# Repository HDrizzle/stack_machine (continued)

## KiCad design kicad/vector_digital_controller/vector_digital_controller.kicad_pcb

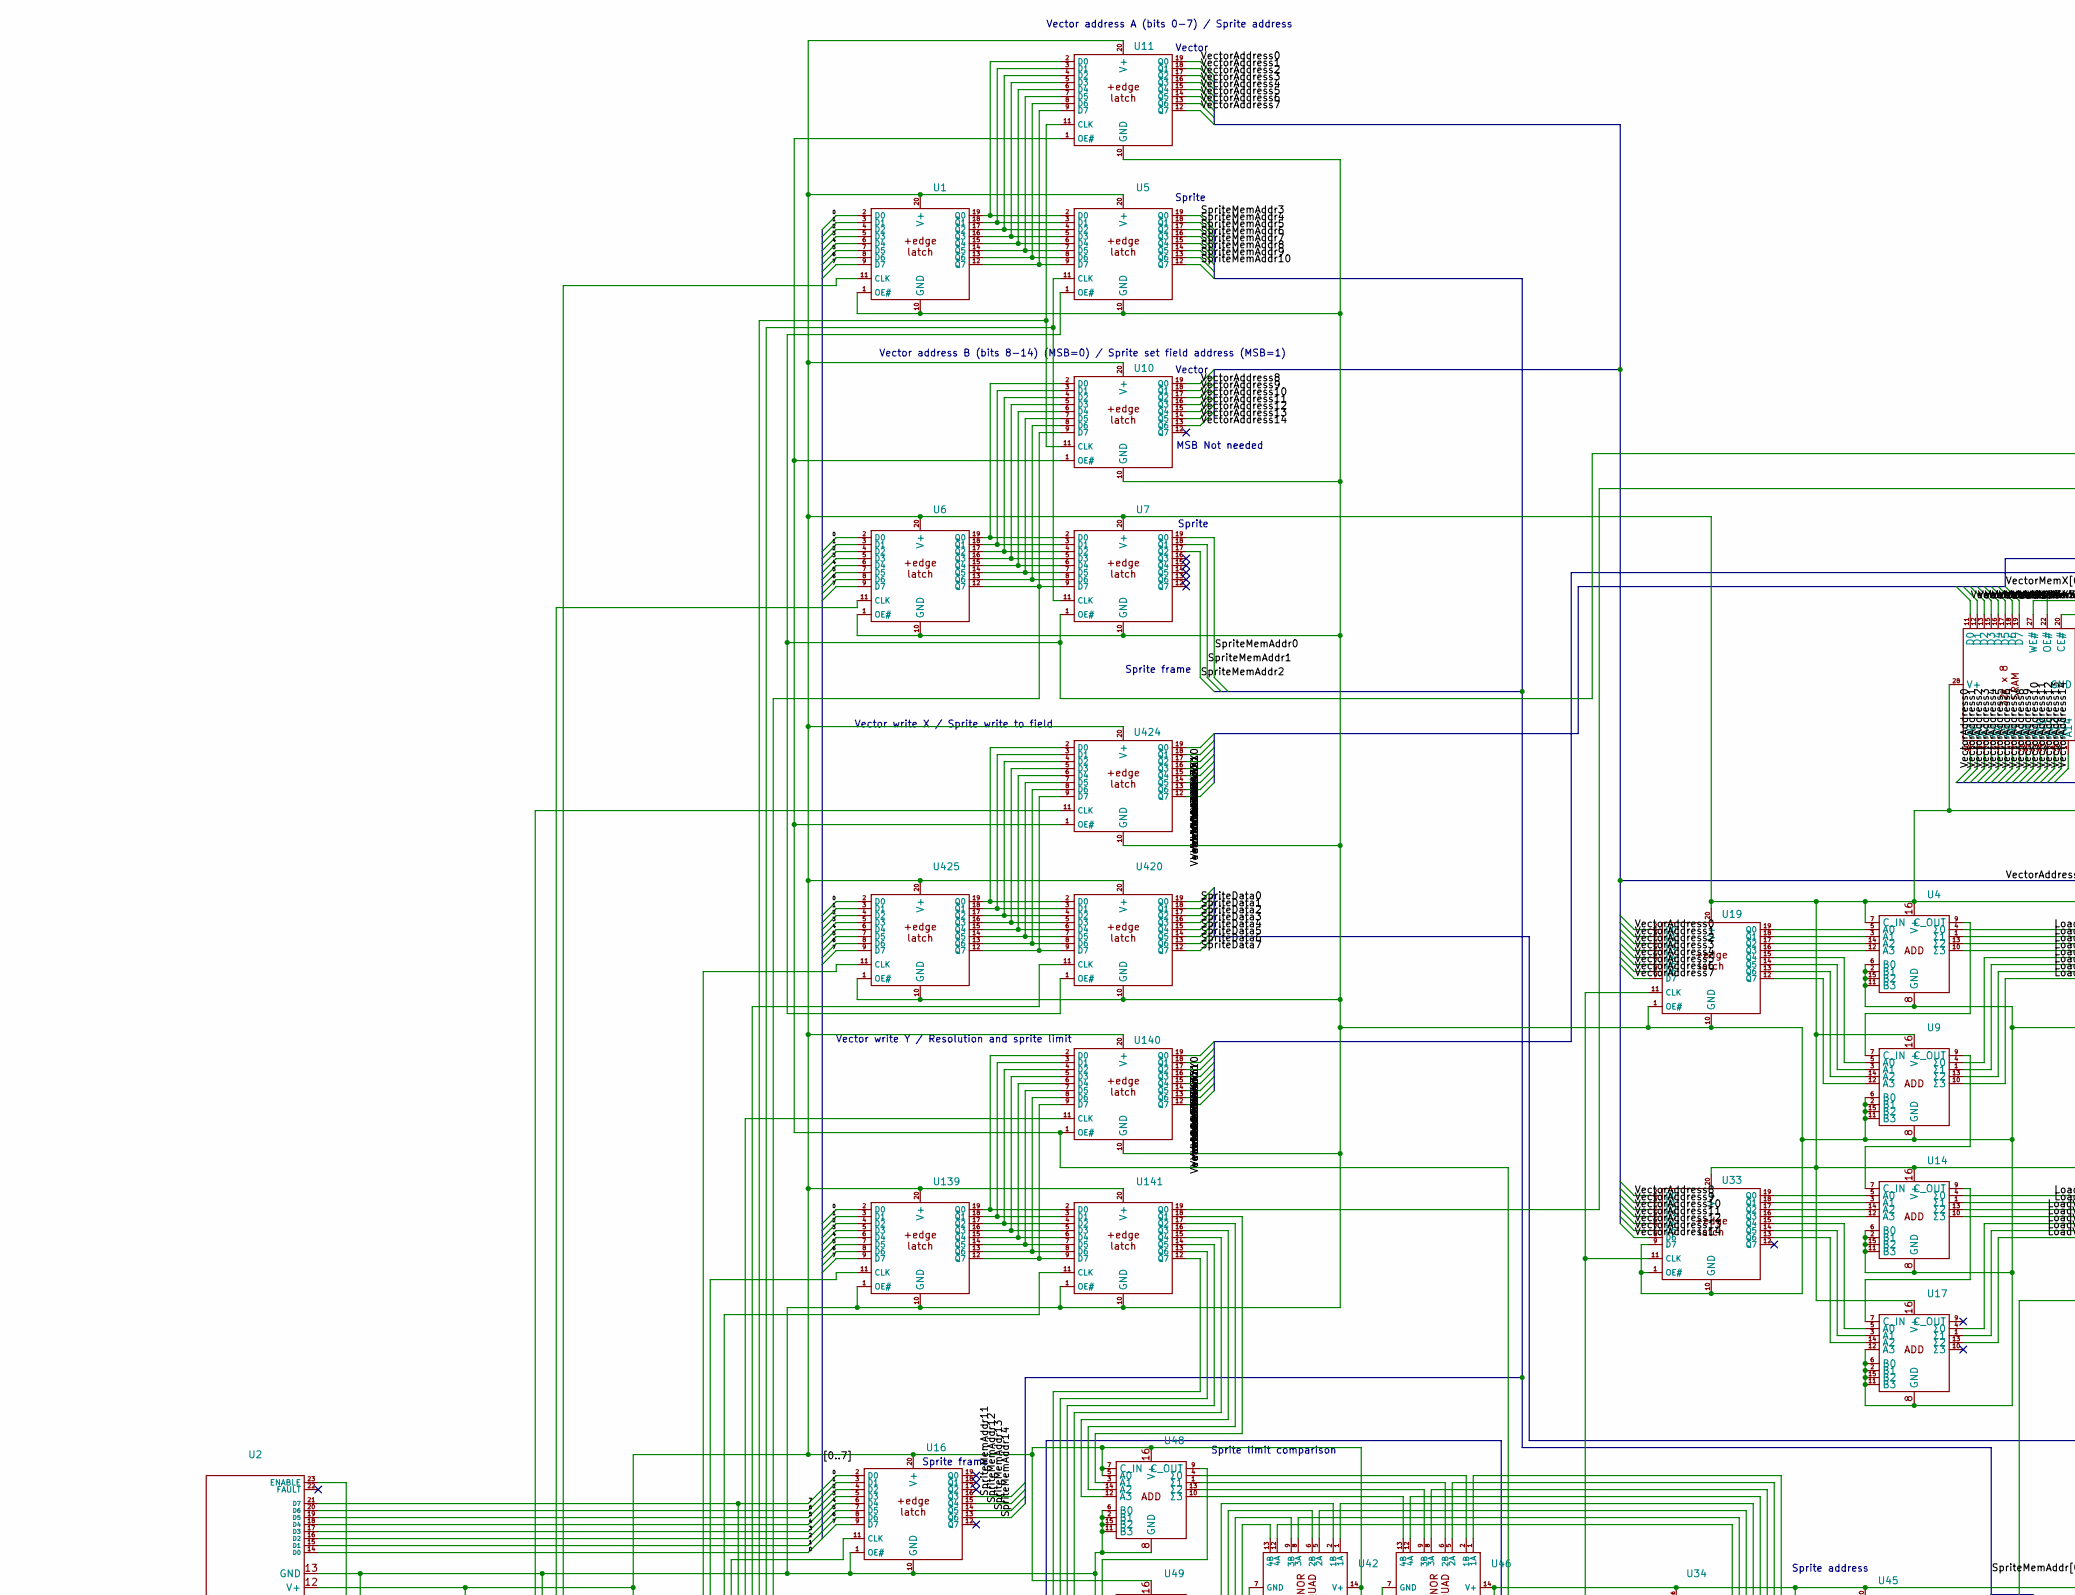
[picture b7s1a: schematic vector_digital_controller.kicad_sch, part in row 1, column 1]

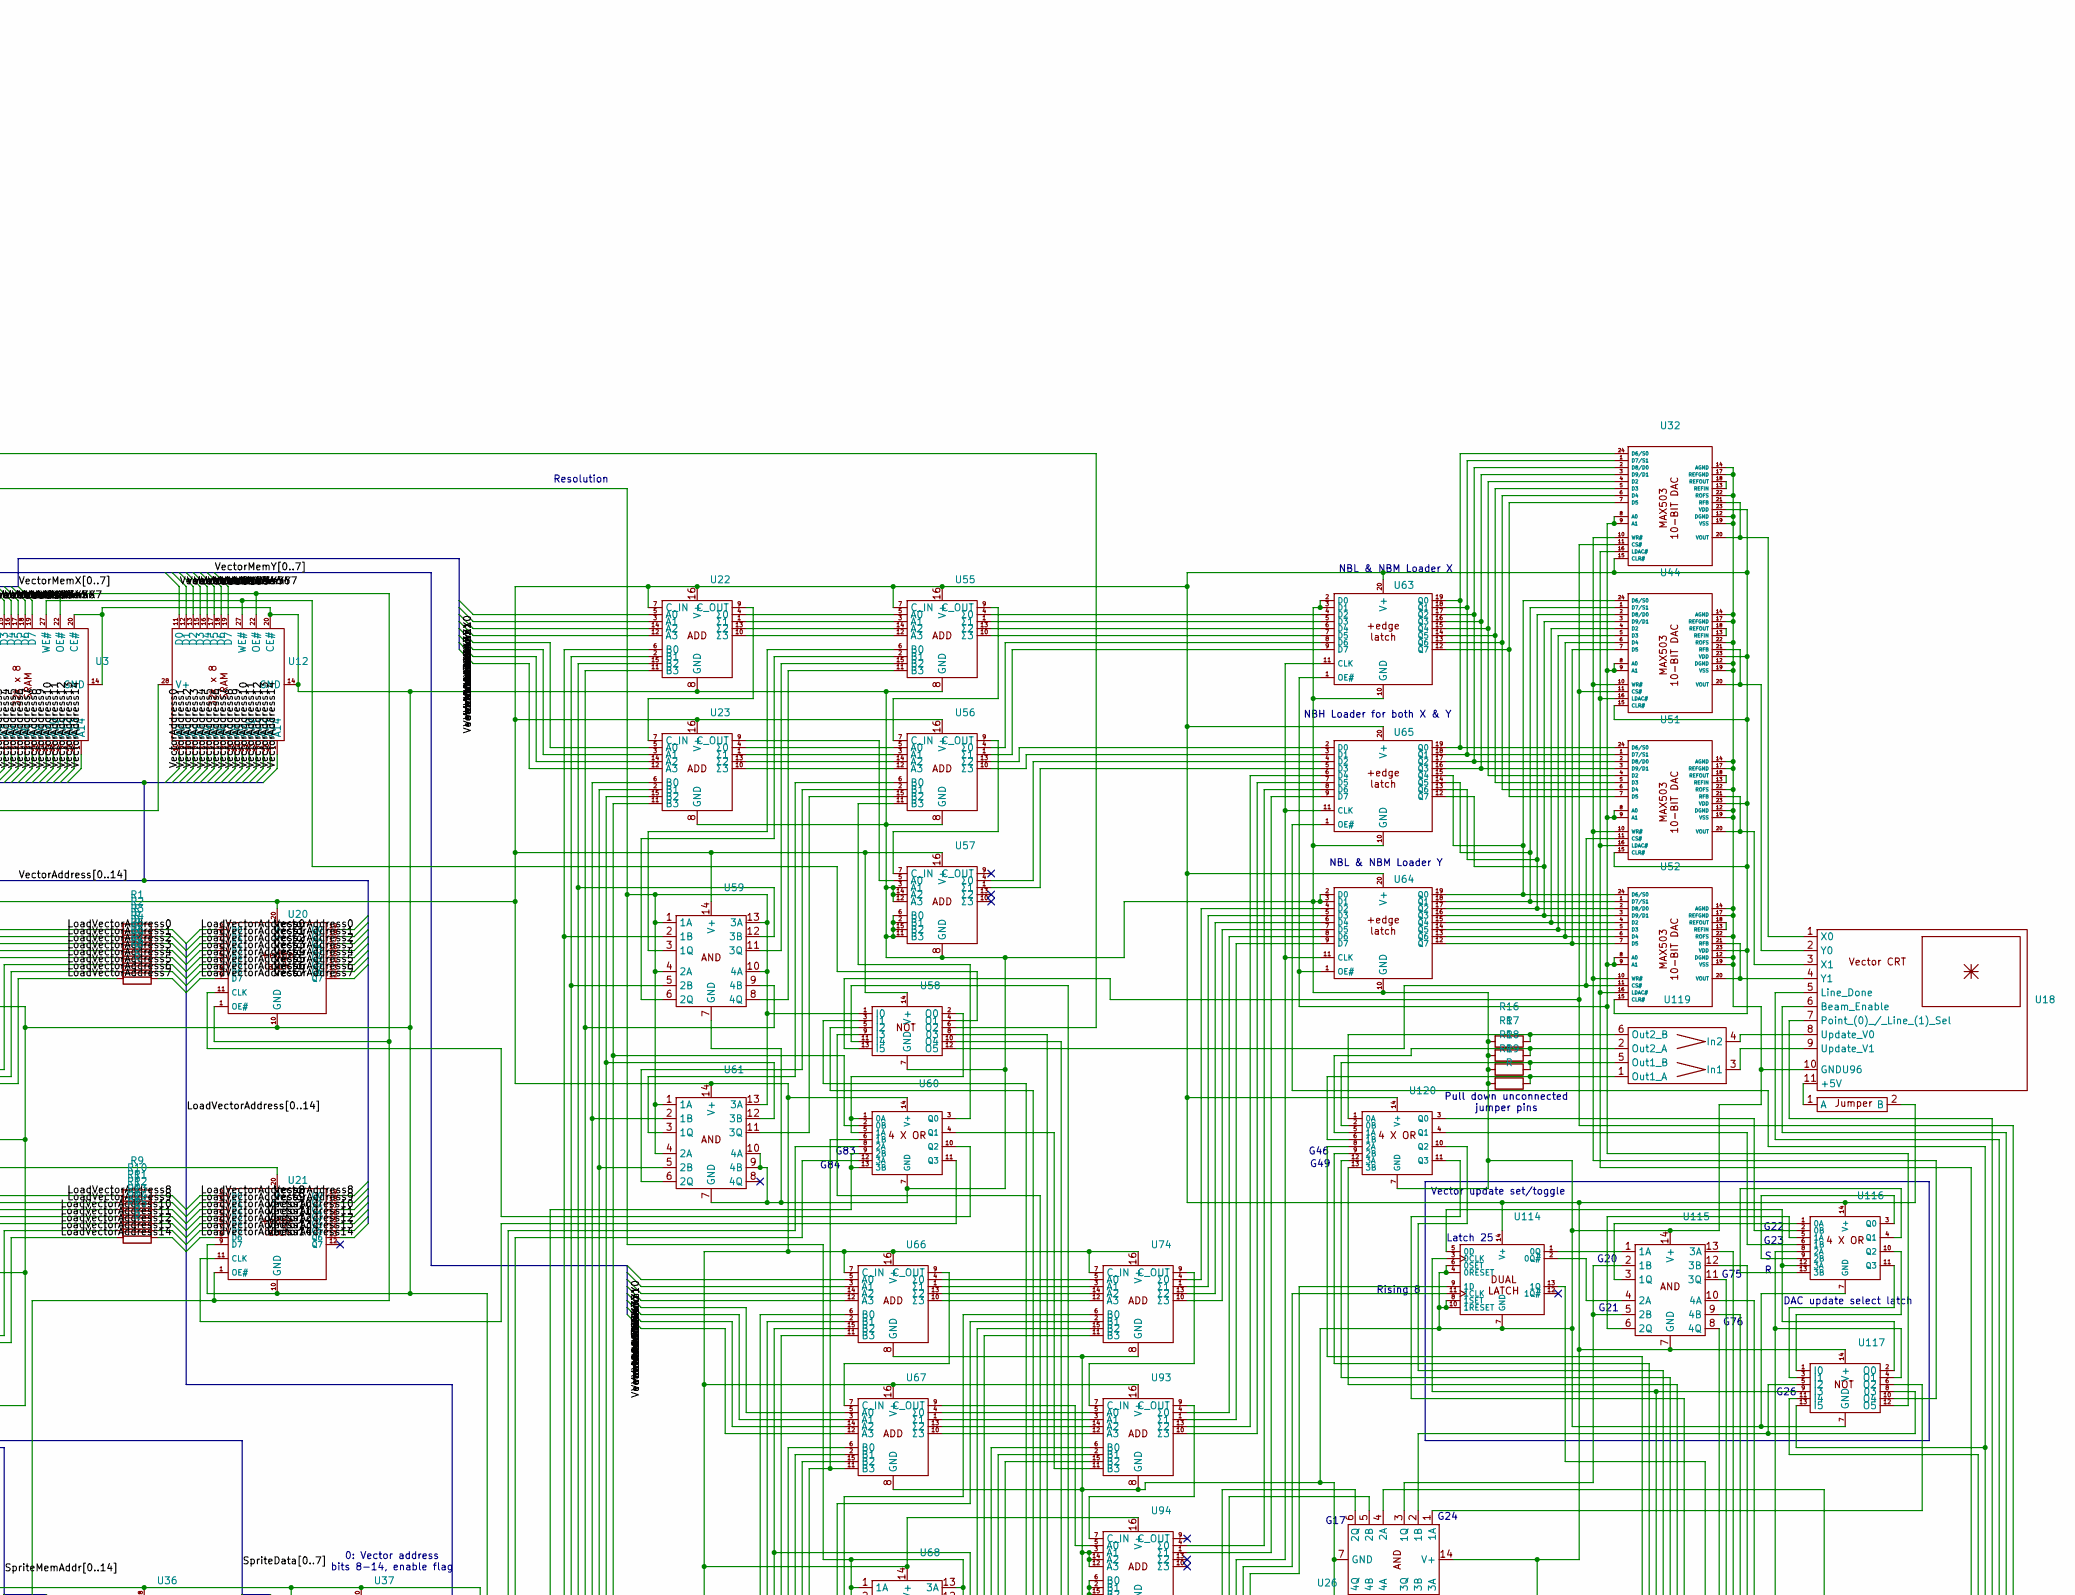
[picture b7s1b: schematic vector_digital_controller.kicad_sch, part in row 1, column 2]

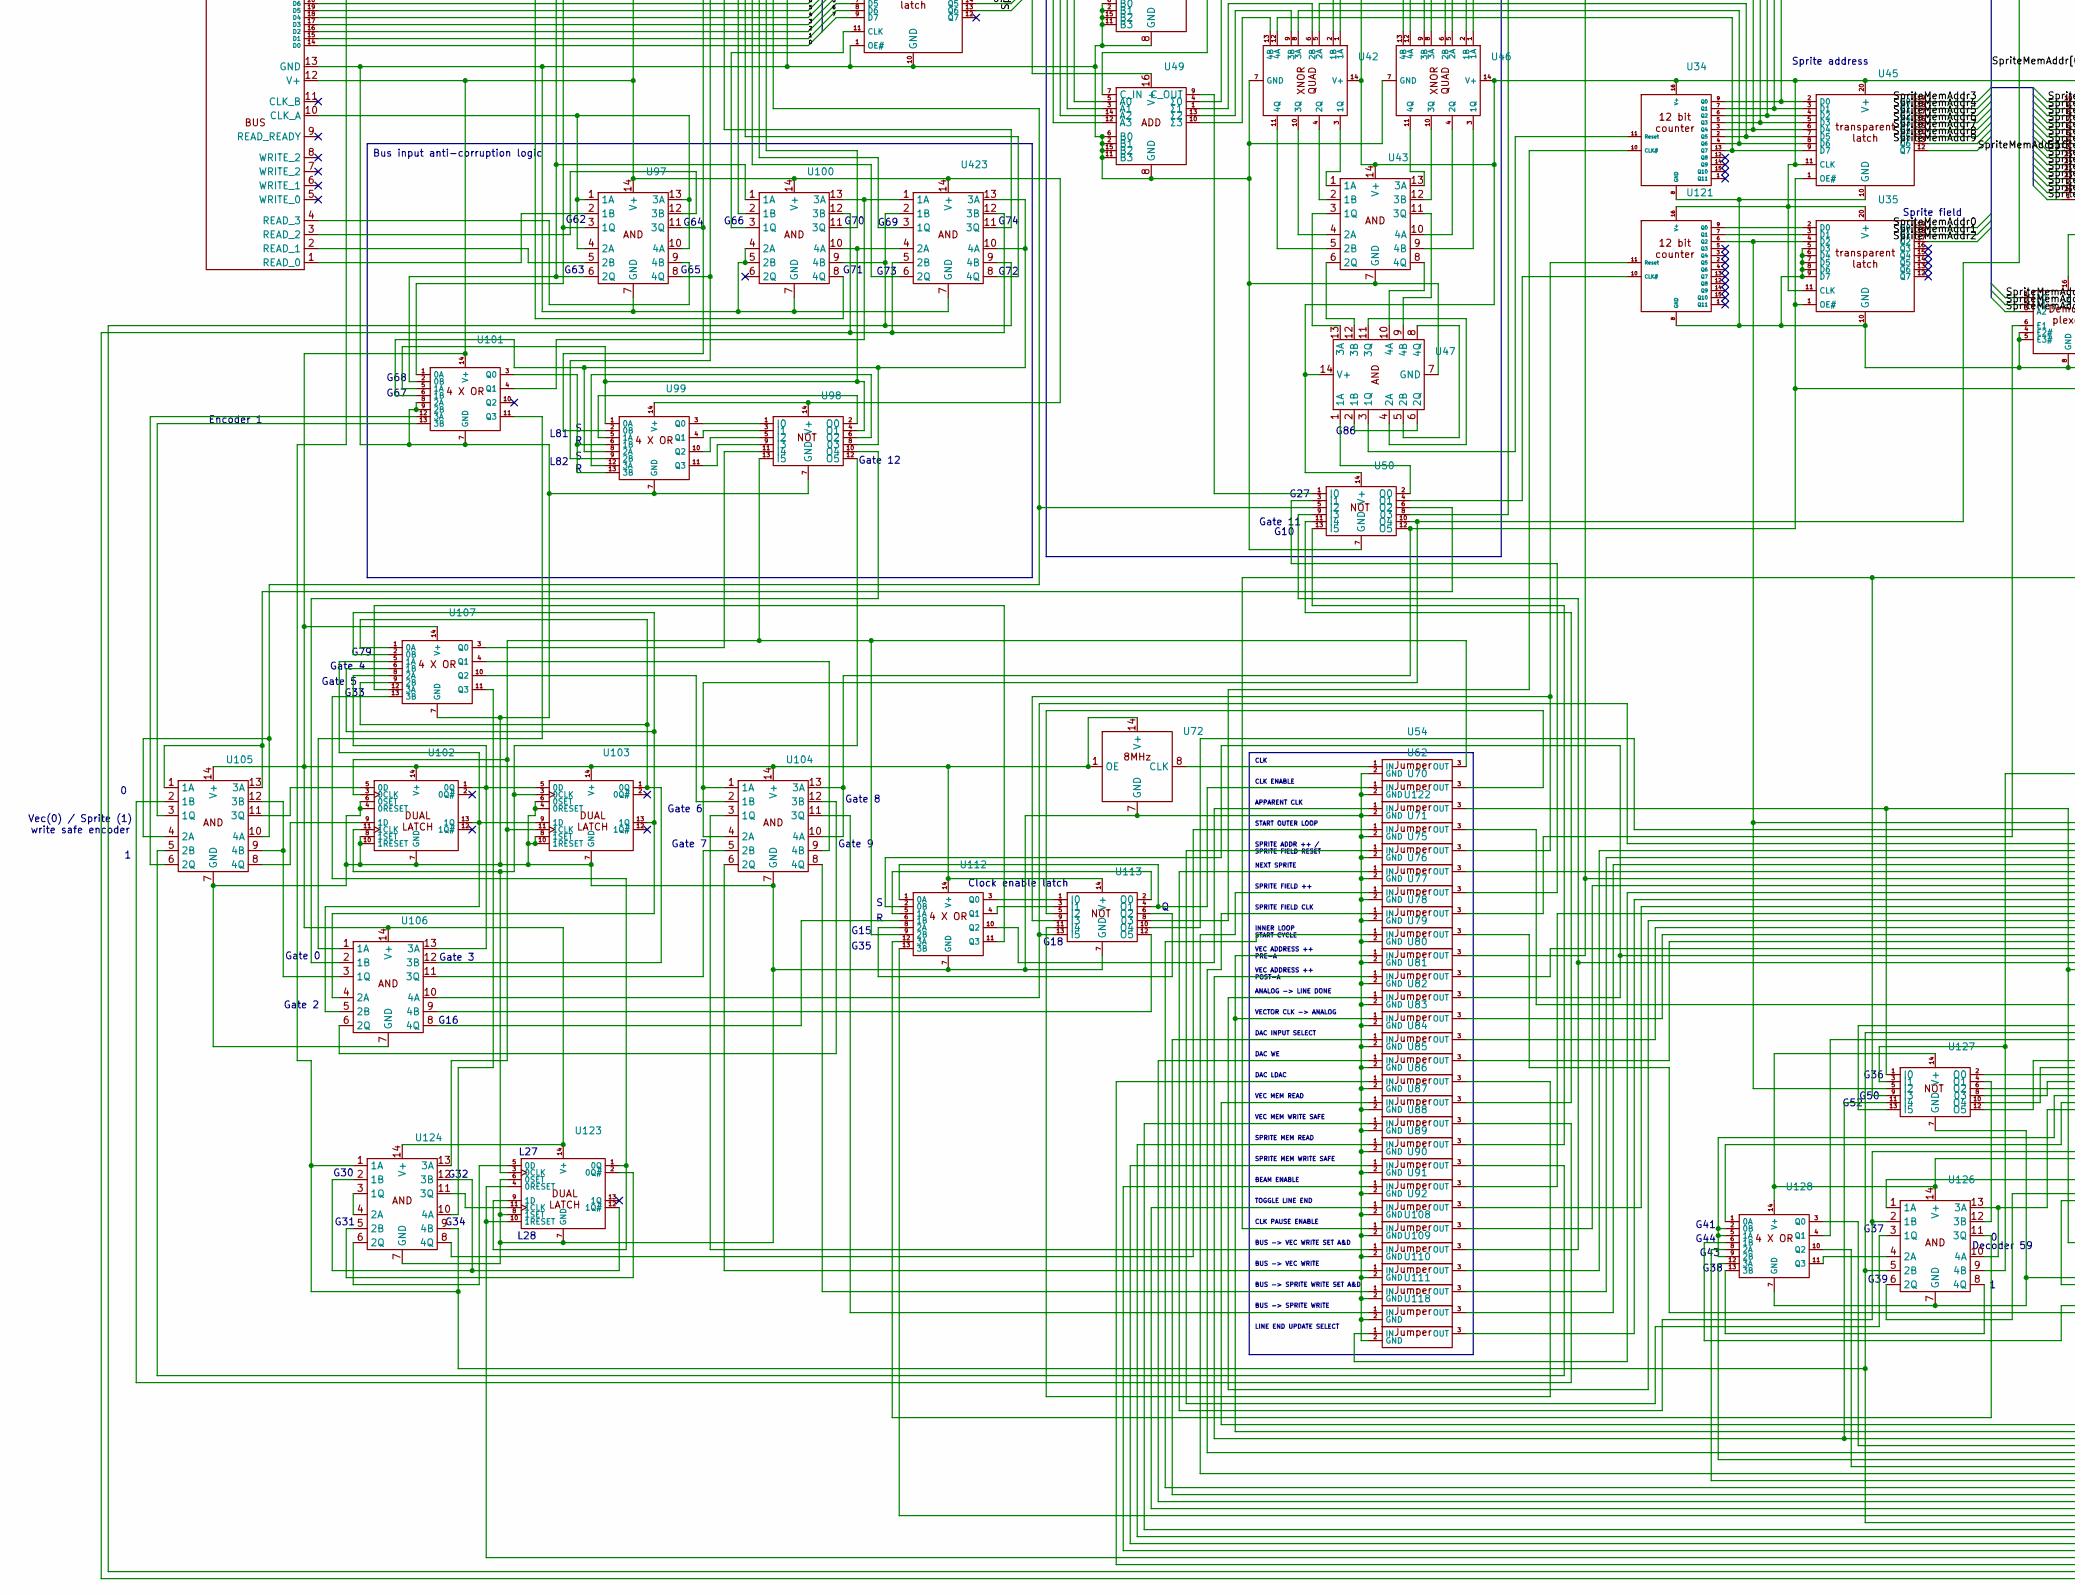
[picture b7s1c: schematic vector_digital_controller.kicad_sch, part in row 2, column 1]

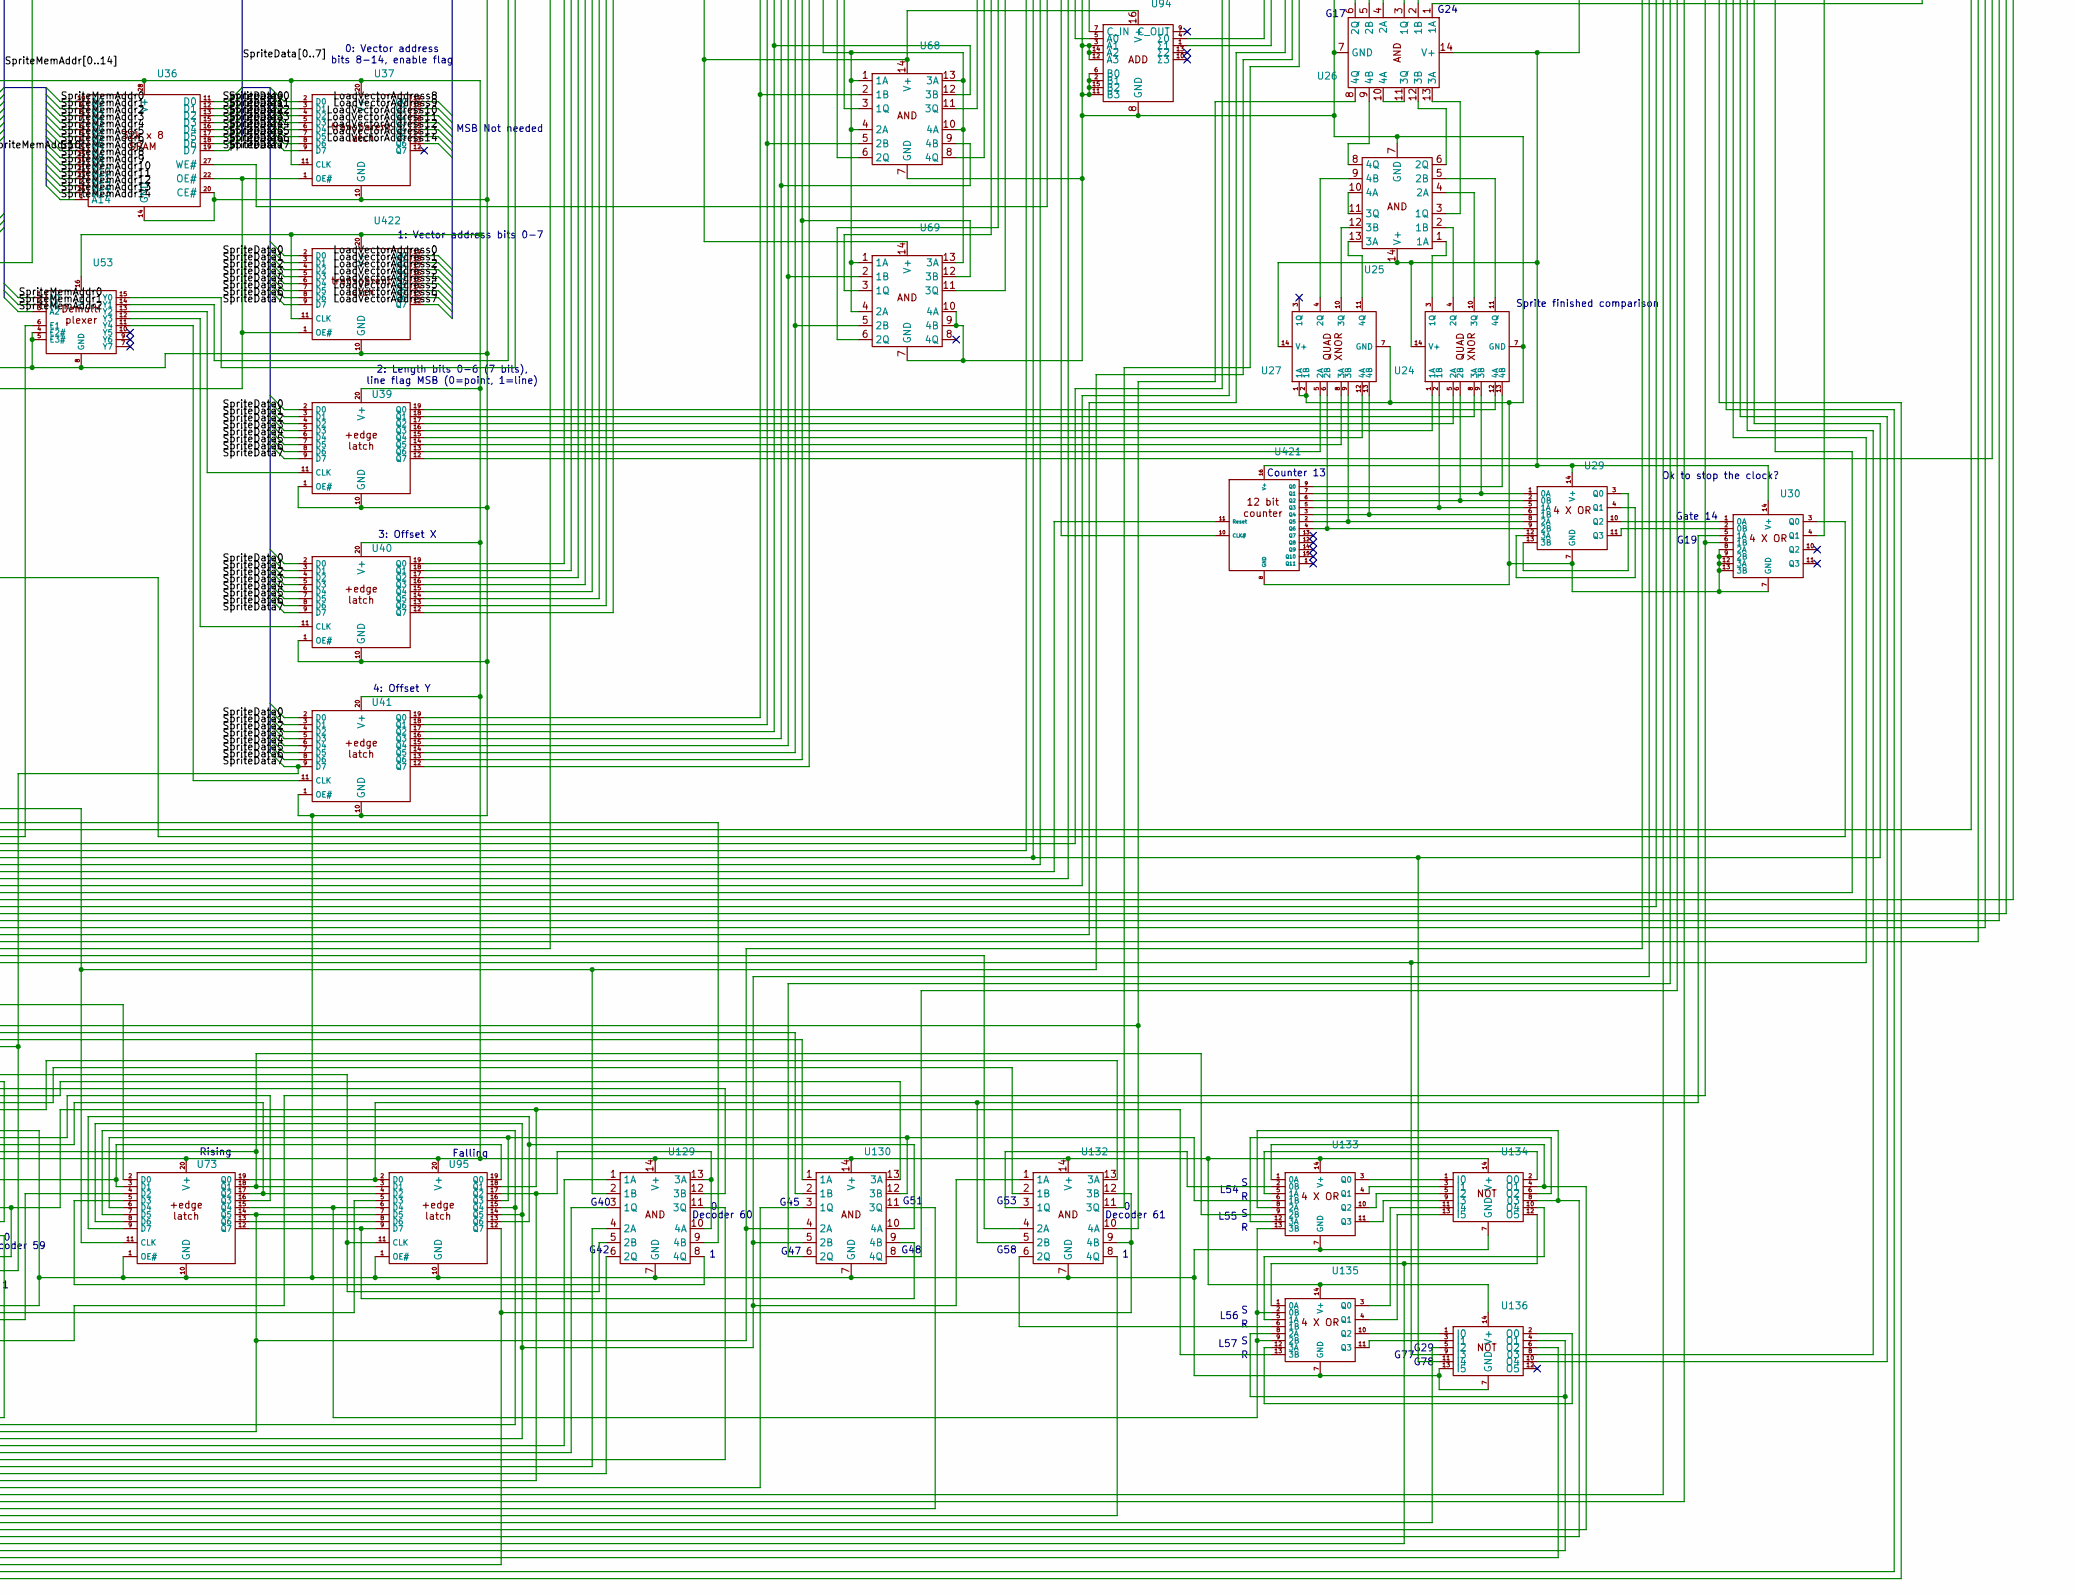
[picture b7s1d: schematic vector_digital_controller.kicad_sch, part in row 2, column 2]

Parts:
R1, R2, R3, R4, R5, R6, R7, R8, R9, R10, R11, R12, R13, R14, R15, R16, R17, R18, R19: R; 0.4_pitch_resistor
U1, U5, U6, U7, U10, U11, U16, U19, U20, U21, U33, U35, U37, U39, U40, U41, U45, U63, U64, U65, U73, U95, U139, U140, U141, U420, U422, U424, U425: DIP-20_W7.62mm
U2: PinHeader_1x23_P2.54mm_Vertical
U3, U12, U36: DIP-28_W15.24mm
U4, U9, U14, U17, U22, U23, U34, U48, U49, U53, U55, U56, U57, U66, U67, U74, U93, U94, U121, U421: DIP-16_W7.62mm
U18: PinHeader_1x11_P2.54mm_Vertical
U24, U25, U26, U27, U29, U30, U42, U43, U46, U47, U50, U58, U59, U60, U61, U68, U69, U97, U98, U99, U100, U101, U102, U103, U104, U105, U106, U107, U112, U113, U114, U115, U116, U117, U120, U123, U124, U126, U127, U128, U129, U130, U132, U133, U134, U135, U136, U423: DIP-14_W7.62mm
U32, U44, U51, U52: DIP-24_W7.62mm
U54, U62, U70, U71, U75, U76, U77, U78, U79, U80, U81, U82, U83, U84, U85, U86, U87, U88, U89, U90, U91, U92, U108, U109, U110, U111, U118, U122: jumper
U72: crystal_dip_14
U96: PinHeader_1x02_P2.54mm_Vertical
U119: PinHeader_2x03_P2.54mm_Vertical

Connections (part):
/0: U1.2 (D0), U2.14 (D0), U6.2 (D0), U16.2 (D0), U139.2 (D0), U425.2 (D0)
/1: U1.3 (D1), U2.15 (D1), U6.3 (D1), U16.3 (D1), U139.3 (D1), U425.3 (D1)
/2: U1.4 (D2), U2.16 (D2), U6.4 (D2), U16.4 (D2), U139.4 (D2), U425.4 (D2)
/3: U1.5 (D3), U2.17 (D3), U6.5 (D3), U16.5 (D3), U139.5 (D3), U425.5 (D3)
/4: U1.6 (D4), U2.18 (D4), U6.6 (D4), U16.6 (D4), U139.6 (D4), U425.6 (D4)
/5: U1.7 (D5), U2.19 (D5), U6.7 (D5), U16.7 (D5), U139.7 (D5), U425.7 (D5)
/6: U1.8 (D6), U2.20 (D6), U6.8 (D6), U16.8 (D6), U139.8 (D6), U425.8 (D6)
/7: U1.9 (D7), U2.21 (D7), U6.9 (D7), U16.9 (D7), U100.2 (1B), U139.9 (D7), U425.9 (D7)
/LoadVectorAddress0: R1.1, U20.2 (D0), U422.19 (Q0)
/LoadVectorAddress1: R2.1, U20.3 (D1), U422.18 (Q1)
/LoadVectorAddress2: R3.1, U20.4 (D2), U422.17 (Q2)
/LoadVectorAddress3: R4.1, U20.5 (D3), U422.16 (Q3)
/LoadVectorAddress4: R5.1, U20.6 (D4), U422.15 (Q4)
/LoadVectorAddress5: R6.1, U20.7 (D5), U422.14 (Q5)
/LoadVectorAddress6: R7.1, U20.8 (D6), U422.13 (Q6)
/LoadVectorAddress7: R8.1, U20.9 (D7), U422.12 (Q7)
/LoadVectorAddress8: R9.1, U21.2 (D0), U37.19 (Q0)
/LoadVectorAddress9: R10.1, U21.3 (D1), U37.18 (Q1)
/LoadVectorAddress10: R11.1, U21.4 (D2), U37.17 (Q2)
/LoadVectorAddress11: R12.1, U21.5 (D3), U37.16 (Q3)
/LoadVectorAddress12: R13.1, U21.6 (D4), U37.15 (Q4)
/LoadVectorAddress13: R14.1, U21.7 (D5), U37.14 (Q5)
/LoadVectorAddress14: R15.1, U21.8 (D6), U37.13 (Q6)
/SpriteData0: U36.11 (D0), U37.2 (D0), U39.2 (D0), U40.2 (D0), U41.2 (D0), U420.19 (Q0), U422.2 (D0)
/SpriteData1: U36.12 (D1), U37.3 (D1), U39.3 (D1), U40.3 (D1), U41.3 (D1), U420.18 (Q1), U422.3 (D1)
/SpriteData2: U36.13 (D2), U37.4 (D2), U39.4 (D2), U40.4 (D2), U41.4 (D2), U420.17 (Q2), U422.4 (D2)
/SpriteData3: U36.15 (D3), U37.5 (D3), U39.5 (D3), U40.5 (D3), U41.5 (D3), U420.16 (Q3), U422.5 (D3)
/SpriteData4: U36.16 (D4), U37.6 (D4), U39.6 (D4), U40.6 (D4), U41.6 (D4), U420.15 (Q4), U422.6 (D4)
/SpriteData5: U36.17 (D5), U37.7 (D5), U39.7 (D5), U40.7 (D5), U41.7 (D5), U420.14 (Q5), U422.7 (D5)
/SpriteData6: U36.18 (D6), U37.8 (D6), U39.8 (D6), U40.8 (D6), U41.8 (D6), U420.13 (Q6), U422.8 (D6)
/SpriteData7: U36.19 (D7), U37.9 (D7), U39.9 (D7), U40.9 (D7), U41.9 (D7), U126.9 (4B), U127.3 (I1), U420.12 (Q7), U422.9 (D7)
/SpriteMemAddr0: U7.19 (Q0), U35.19 (Q0), U36.10 (A0), U53.1 (A0)
/SpriteMemAddr1: U7.18 (Q1), U35.18 (Q1), U36.9 (A1), U53.2 (A1)
/SpriteMemAddr2: U7.17 (Q2), U35.17 (Q2), U36.8 (A2), U53.3 (A2)
/SpriteMemAddr3: U5.19 (Q0), U36.7 (A3), U45.19 (Q0)
/SpriteMemAddr4: U5.18 (Q1), U36.6 (A4), U45.18 (Q1)
/SpriteMemAddr5: U5.17 (Q2), U36.5 (A5), U45.17 (Q2)
/SpriteMemAddr6: U5.16 (Q3), U36.4 (A6), U45.16 (Q3)
/SpriteMemAddr7: U5.15 (Q4), U36.3 (A7), U45.15 (Q4)
/SpriteMemAddr8: U5.14 (Q5), U36.25 (A8), U45.14 (Q5)
/SpriteMemAddr9: U5.13 (Q6), U36.24 (A9), U45.13 (Q6)
/SpriteMemAddr10: U5.12 (Q7), U36.21 (A10), U45.12 (Q7)
/SpriteMemAddr11: U16.16 (Q3), U36.23 (A11)
/SpriteMemAddr12: U16.15 (Q4), U36.2 (A12)
/SpriteMemAddr13: U16.14 (Q5), U36.26 (A13)
/SpriteMemAddr14: U16.13 (Q6), U36.1 (A14)
/VectorAddress0: U3.10 (A0), U11.19 (Q0), U12.10 (A0), U19.2 (D0), U20.19 (Q0)
/VectorAddress1: U3.9 (A1), U11.18 (Q1), U12.9 (A1), U19.3 (D1), U20.18 (Q1)
/VectorAddress2: U3.8 (A2), U11.17 (Q2), U12.8 (A2), U19.4 (D2), U20.17 (Q2)
/VectorAddress3: U3.7 (A3), U11.16 (Q3), U12.7 (A3), U19.5 (D3), U20.16 (Q3)
/VectorAddress4: U3.6 (A4), U11.15 (Q4), U12.6 (A4), U19.6 (D4), U20.15 (Q4)
/VectorAddress5: U3.5 (A5), U11.14 (Q5), U12.5 (A5), U19.7 (D5), U20.14 (Q5)
/VectorAddress6: U3.4 (A6), U11.13 (Q6), U12.4 (A6), U19.8 (D6), U20.13 (Q6)
/VectorAddress7: U3.3 (A7), U11.12 (Q7), U12.3 (A7), U19.9 (D7), U20.12 (Q7)
/VectorAddress8: U3.25 (A8), U10.19 (Q0), U12.25 (A8), U21.19 (Q0), U33.2 (D0)
/VectorAddress9: U3.24 (A9), U10.18 (Q1), U12.24 (A9), U21.18 (Q1), U33.3 (D1)
/VectorAddress10: U3.21 (A10), U10.17 (Q2), U12.21 (A10), U21.17 (Q2), U33.4 (D2)
/VectorAddress11: U3.23 (A11), U10.16 (Q3), U12.23 (A11), U21.16 (Q3), U33.5 (D3)
/VectorAddress12: U3.2 (A12), U10.15 (Q4), U12.2 (A12), U21.15 (Q4), U33.6 (D4)
/VectorAddress13: U3.26 (A13), U10.14 (Q5), U12.26 (A13), U21.14 (Q5), U33.7 (D5)
/VectorAddress14: U3.1 (A14), U10.13 (Q6), U12.1 (A14), U21.13 (Q6), U33.8 (D6)
/VectorMemX0: U3.11 (D0), U22.5 (A0), U424.19 (Q0)
/VectorMemX1: U3.12 (D1), U22.3 (A1), U424.18 (Q1)
/VectorMemX2: U3.13 (D2), U22.14 (A2), U424.17 (Q2)
/VectorMemX3: U3.15 (D3), U22.12 (A3), U424.16 (Q3)
/VectorMemX4: U3.16 (D4), U23.5 (A0), U424.15 (Q4)
/VectorMemX5: U3.17 (D5), U23.3 (A1), U424.14 (Q5)
/VectorMemX6: U3.18 (D6), U23.14 (A2), U424.13 (Q6)
/VectorMemX7: U3.19 (D7), U23.12 (A3), U424.12 (Q7)
/VectorMemY0: U12.11 (D0), U66.5 (A0), U140.19 (Q0)
/VectorMemY1: U12.12 (D1), U66.3 (A1), U140.18 (Q1)
/VectorMemY2: U12.13 (D2), U66.14 (A2), U140.17 (Q2)
/VectorMemY3: U12.15 (D3), U66.12 (A3), U140.16 (Q3)
/VectorMemY4: U12.16 (D4), U67.5 (A0), U140.15 (Q4)
/VectorMemY5: U12.17 (D5), U67.3 (A1), U140.14 (Q5)
/VectorMemY6: U12.18 (D6), U67.14 (A2), U140.13 (Q6)
/VectorMemY7: U12.19 (D7), U67.12 (A3), U140.12 (Q7)
unnamed: U1.11 (CLK), U97.3 (1Q), U101.1 (0A)
unnamed: R16.2, R17.2, R18.2, R19.2, U1.1 (OE#), U1.10 (GND), U2.13 (GND), U3.14 (GND), U3.20 (CE#), U4.2 (B1), U4.6 (B0), U4.8 (GND), U4.11 (B3), U4.15 (B2), U5.10 (GND), U6.1 (OE#), U6.10 (GND), U7.10 (GND), U9.2 (B1), U9.6 (B0), U9.8 (GND), U9.11 (B3), U9.15 (B2), U10.10 (GND), U11.10 (GND), U12.14 (GND), U12.20 (CE#), U14.2 (B1), U14.6 (B0), U14.8 (GND), U14.11 (B3), U14.15 (B2), U16.1 (OE#), U16.10 (GND), U17.2 (B1), U17.6 (B0), U17.8 (GND), U17.11 (B3), U17.12 (A3), U17.15 (B2), U18.10 (GND), U19.1 (OE#), U19.10 (GND), U20.10 (GND), U21.9 (D7), U21.10 (GND), U22.8 (GND), U23.8 (GND), U24.7 (GND), U25.7 (GND), U26.7 (GND), U27.1 (1A), U27.2 (1B), U27.7 (GND), U29.7 (GND), U30.7 (GND), U30.8 (2A), U30.9 (2B), U30.12 (3A), U30.13 (3B), U32.12 (DGND), U32.14 (AGND), U32.17 (REFGND), U32.19 (VSS), U32.22 (ROFS), U33.1 (OE#), U33.9 (D7), U33.10 (GND), U34.8 (GND), U35.5 (D3), U35.6 (D4), U35.7 (D5), U35.8 (D6), U35.9 (D7), U35.10 (GND), U36.14 (GND), U36.20 (CE#), U37.10 (GND), U39.1 (OE#), U39.10 (GND), U40.1 (OE#), U40.10 (GND)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
unnamed: U1.19 (Q0), U5.2 (D0), U11.2 (D0)
unnamed: U1.18 (Q1), U5.3 (D1), U11.3 (D1)
unnamed: U1.17 (Q2), U5.4 (D2), U11.4 (D2)
unnamed: U1.16 (Q3), U5.5 (D3), U11.5 (D3)
unnamed: U1.15 (Q4), U5.6 (D4), U11.6 (D4)
unnamed: U1.14 (Q5), U5.7 (D5), U11.7 (D5)
unnamed: U1.13 (Q6), U5.8 (D6), U11.8 (D6)
unnamed: U1.12 (Q7), U5.9 (D7), U11.9 (D7)
unnamed: U1.20 (V+), U2.12 (V+), U3.28 (V+), U4.7 (C_IN), U4.16 (V+), U5.20 (V+), U6.20 (V+), U7.20 (V+), U9.16 (V+), U10.20 (V+), U11.20 (V+), U12.28 (V+), U14.16 (V+), U16.20 (V+), U17.16 (V+), U19.20 (V+), U20.20 (V+), U21.20 (V+), U22.7 (C_IN), U22.16 (V+), U23.16 (V+), U24.14 (V+), U25.14 (V+), U26.14 (V+), U27.14 (V+), U29.14 (V+), U30.14 (V+), U32.15 (CLR#), U32.23 (VDD), U33.20 (V+), U34.16 (V+), U35.11 (CLK), U35.20 (V+), U36.28 (V+), U37.11 (CLK), U37.20 (V+), U39.20 (V+), U40.20 (V+), U41.20 (V+), U42.14 (V+), U43.14 (V+), U44.15 (CLR#), U44.23 (VDD), U45.11 (CLK), U45.20 (V+), U46.14 (V+), U47.14 (V+), U48.5 (A0), U48.7 (C_IN), U48.16 (V+), U49.16 (V+), U50.14 (V+), U51.15 (CLR#), U51.23 (VDD), U52.15 (CLR#), U52.23 (VDD), U53.16 (V+), U55.7 (C_IN), U55.16 (V+), U56.16 (V+), U57.16 (V+), U58.14 (V+), U59.14 (V+), U60.14 (V+), U61.14 (V+), U63.20 (V+), U64.20 (V+), U65.20 (V+), U66.7 (C_IN), U66.16 (V+), U67.16 (V+), U68.14 (V+), U69.14 (V+), U72.1 (OE), U72.14 (V+), U73.20 (V+), U74.7 (C_IN), U74.16 (V+), U93.16 (V+), U94.16 (V+), U95.20 (V+), U96.2 (B)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
unnamed: U2.10 (CLK_A), U97.1 (1A), U97.4 (2A), U97.10 (4A), U97.13 (3A)
unnamed: U2.1 (READ_0), U97.2 (1B)
unnamed: U2.2 (READ_1), U97.5 (2B)
unnamed: U2.3 (READ_2), U97.12 (3B)
unnamed: U2.4 (READ_3), U97.9 (4B)
unnamed: U4.9 (C_OUT), U9.7 (C_IN)
unnamed: R1.2, U4.4 (Σ0)
unnamed: R2.2, U4.1 (Σ1)
unnamed: R3.2, U4.13 (Σ2)
unnamed: R4.2, U4.10 (Σ3)
unnamed: R5.2, U9.4 (Σ0)
unnamed: R6.2, U9.1 (Σ1)
unnamed: R7.2, U9.13 (Σ2)
unnamed: R8.2, U9.10 (Σ3)
unnamed: U10.11 (CLK), U11.11 (CLK), U423.3 (1Q)
unnamed: U6.19 (Q0), U7.2 (D0), U10.2 (D0)
unnamed: U6.18 (Q1), U7.3 (D1), U10.3 (D1)
unnamed: U6.17 (Q2), U7.4 (D2), U10.4 (D2)
unnamed: U6.16 (Q3), U7.5 (D3), U10.5 (D3)
unnamed: U6.15 (Q4), U7.6 (D4), U10.6 (D4)
unnamed: U6.14 (Q5), U7.7 (D5), U10.7 (D5)
unnamed: U6.13 (Q6), U7.8 (D6), U10.8 (D6)
unnamed: U6.12 (Q7), U7.9 (D7), U10.9 (D7), U50.5 (I2), U105.4 (2A), U105.10 (4A)
unnamed: U10.1 (OE#), U11.1 (OE#), U50.8 (03), U140.1 (OE#), U424.1 (OE#)
unnamed: U3.27 (WE#), U12.27 (WE#), U58.4 (O1)
unnamed: U14.5 (A0), U33.19 (Q0)
unnamed: U14.3 (A1), U33.18 (Q1)
unnamed: U14.14 (A2), U33.17 (Q2)
unnamed: U14.12 (A3), U33.16 (Q3)
unnamed: U9.9 (C_OUT), U14.7 (C_IN)
unnamed: U14.9 (C_OUT), U17.7 (C_IN)
unnamed: R9.2, U14.4 (Σ0)
unnamed: R10.2, U14.1 (Σ1)
unnamed: R11.2, U14.13 (Σ2)
unnamed: R12.2, U14.10 (Σ3)
unnamed: U17.5 (A0), U33.15 (Q4)
unnamed: U17.3 (A1), U33.14 (Q5)
unnamed: U17.14 (A2), U33.13 (Q6)
unnamed: R13.2, U17.4 (Σ0)
unnamed: R14.2, U17.1 (Σ1)
unnamed: R15.2, U17.13 (Σ2)
unnamed: U18.11 (+5V), U96.1 (A)
unnamed: U18.6 (Beam_Enable), U90.3 (OUT)
unnamed: U18.5 (Line_Done), U81.1 (IN)
unnamed: U18.7 (Point_(0)_/_Line_(1)_Sel), U39.12 (Q7)
unnamed: U18.1 (X0), U32.20 (VOUT), U32.21 (RFB)
unnamed: U18.3 (X1), U51.20 (VOUT), U51.21 (RFB)
unnamed: U18.2 (Y0), U44.20 (VOUT), U44.21 (RFB)
unnamed: U18.4 (Y1), U52.20 (VOUT), U52.21 (RFB)
unnamed: U19.11 (CLK), U33.11 (CLK), U58.11 (I4), U79.3 (OUT)
unnamed: U4.5 (A0), U19.19 (Q0)
unnamed: U4.3 (A1), U19.18 (Q1)
unnamed: U4.14 (A2), U19.17 (Q2)
unnamed: U4.12 (A3), U19.16 (Q3)
unnamed: U9.5 (A0), U19.15 (Q4)
unnamed: U9.3 (A1), U19.14 (Q5)
unnamed: U9.14 (A2), U19.13 (Q6)
unnamed: U9.12 (A3), U19.12 (Q7)
unnamed: U20.11 (CLK), U60.10 (Q2)
unnamed: U21.11 (CLK), U60.11 (Q3)
unnamed: U22.6 (B0), U40.19 (Q0), U59.2 (1B)
unnamed: U22.2 (B1), U40.18 (Q1), U59.5 (2B)
unnamed: U22.15 (B2), U40.17 (Q2), U59.12 (3B)
unnamed: U22.11 (B3), U40.16 (Q3), U59.9 (4B)
unnamed: U22.9 (C_OUT), U23.7 (C_IN)
unnamed: U22.4 (Σ0), U55.5 (A0)
unnamed: U22.1 (Σ1), U55.3 (A1)
unnamed: U22.13 (Σ2), U55.14 (A2)
unnamed: U22.10 (Σ3), U55.12 (A3)
unnamed: U23.6 (B0), U40.15 (Q4), U61.2 (1B)
unnamed: U23.2 (B1), U40.14 (Q5), U61.5 (2B)
unnamed: U23.15 (B2), U40.13 (Q6), U61.12 (3B)
unnamed: U23.11 (B3), U40.12 (Q7), U60.2 (0B)
unnamed: U23.9 (C_OUT), U57.5 (A0)
unnamed: U23.4 (Σ0), U56.5 (A0)
unnamed: U23.1 (Σ1), U56.3 (A1)
unnamed: U23.13 (Σ2), U56.14 (A2)
unnamed: U23.10 (Σ3), U56.12 (A3)
unnamed: U24.1 (1A), U39.16 (Q3)
unnamed: U24.2 (1B), U29.5 (1A), U421.5 (Q3)
unnamed: U24.3 (1Q), U25.1 (1A)
unnamed: U24.5 (2A), U39.17 (Q2)
unnamed: U24.6 (2B), U29.2 (0B), U421.6 (Q2)
unnamed: U24.4 (2Q), U25.2 (1B)
unnamed: U24.8 (3A), U39.18 (Q1)
unnamed: U24.9 (3B), U29.1 (0A), U421.7 (Q1)
unnamed: U24.10 (3Q), U25.4 (2A)
unnamed: U24.12 (4A), U39.19 (Q0)
unnamed: U24.13 (4B), U421.9 (Q0)
unnamed: U24.11 (4Q), U25.5 (2B)
unnamed: U25.3 (1Q), U26.13 (3A)
unnamed: U25.6 (2Q), U26.12 (3B)
unnamed: U25.13 (3A), U27.11 (4Q)
unnamed: U25.12 (3B), U27.10 (3Q)
unnamed: U25.10 (4A), U25.11 (3Q)
unnamed: U25.9 (4B), U27.4 (2Q)
unnamed: U25.8 (4Q), U26.9 (4B)
unnamed: U26.4 (2A), U30.4 (Q1)
unnamed: U26.5 (2B), U92.3 (OUT)
unnamed: U26.10 (4A), U26.11 (3Q)
unnamed: U27.5 (2A), U39.13 (Q6)
unnamed: U27.6 (2B), U29.9 (2B), U421.4 (Q6)
unnamed: U27.8 (3A), U39.14 (Q5)
unnamed: U27.9 (3B), U29.8 (2A), U421.2 (Q5)
unnamed: U27.12 (4A), U39.15 (Q4)
unnamed: U27.13 (4B), U29.6 (1B), U421.3 (Q4)
unnamed: U29.4 (Q1), U29.12 (3A)
unnamed: U29.3 (Q0), U29.13 (3B)
unnamed: U29.10 (Q2), U30.1 (0A)
unnamed: U29.11 (Q3), U30.2 (0B)
unnamed: U32.4 (D2), U51.4 (D2), U63.15 (Q4)
unnamed: U32.5 (D3), U51.5 (D3), U63.14 (Q5)
unnamed: U32.6 (D4), U51.6 (D4), U63.13 (Q6)
unnamed: U32.7 (D5), U51.7 (D5), U63.12 (Q7)
unnamed: U32.24 (D6/S0), U51.24 (D6/S0), U63.19 (Q0), U65.19 (Q0)
unnamed: U32.1 (D7/S1), U51.1 (D7/S1), U63.18 (Q1), U65.18 (Q1)
unnamed: U32.2 (D8/D0), U51.2 (D8/D0), U63.17 (Q2), U65.17 (Q2)
unnamed: U32.3 (D9/D1), U51.3 (D9/D1), U63.16 (Q3), U65.16 (Q3)
unnamed: U32.13 (REFIN), U32.18 (REFOUT)
unnamed: U34.9 (Q0), U45.2 (D0), U46.1 (1A)
unnamed: U34.7 (Q1), U45.3 (D1), U46.5 (2A)
unnamed: U34.6 (Q2), U45.4 (D2), U46.8 (3A)
unnamed: U34.5 (Q3), U45.5 (D3), U46.12 (4A)
unnamed: U34.3 (Q4), U42.1 (1A), U45.6 (D4)
unnamed: U34.2 (Q5), U42.5 (2A), U45.7 (D5)
unnamed: U34.4 (Q6), U42.8 (3A), U45.8 (D6)
unnamed: U34.13 (Q7), U42.12 (4A), U45.9 (D7)
unnamed: U34.11 (Reset), U47.3 (1Q)
unnamed: U36.27 (WE#), U58.8 (03)
unnamed: U39.11 (CLK), U53.13 (Y2)
unnamed: U40.11 (CLK), U53.12 (Y3)
unnamed: U41.11 (CLK), U53.11 (Y4)
unnamed: U41.19 (Q0), U66.6 (B0), U68.2 (1B)
unnamed: U41.18 (Q1), U66.2 (B1), U68.5 (2B)
unnamed: U41.17 (Q2), U66.15 (B2), U68.12 (3B)
unnamed: U41.16 (Q3), U66.11 (B3), U68.9 (4B)
unnamed: U41.15 (Q4), U67.6 (B0), U69.2 (1B)
unnamed: U41.14 (Q5), U67.2 (B1), U69.5 (2B)
unnamed: U41.13 (Q6), U67.15 (B2), U69.12 (3B)
unnamed: U41.12 (Q7), U60.6 (1B), U67.11 (B3)
unnamed: U42.2 (1B), U49.4 (Σ0)
unnamed: U42.3 (1Q), U43.1 (1A)
unnamed: U42.6 (2B), U49.1 (Σ1)
unnamed: U42.4 (2Q), U43.2 (1B)
unnamed: U42.9 (3B), U49.13 (Σ2)
unnamed: U42.10 (3Q), U43.4 (2A)
unnamed: U42.13 (4B), U49.10 (Σ3)
unnamed: U42.11 (4Q), U43.5 (2B)
unnamed: U43.3 (1Q), U47.13 (3A)
unnamed: U43.6 (2Q), U47.12 (3B)
unnamed: U43.13 (3A), U46.11 (4Q)
unnamed: U43.12 (3B), U46.10 (3Q)
unnamed: U43.11 (3Q), U47.9 (4B)
unnamed: U43.10 (4A), U46.4 (2Q)
unnamed: U43.9 (4B), U46.3 (1Q)
unnamed: U43.8 (4Q), U47.10 (4A)
unnamed: U44.4 (D2), U52.4 (D2), U64.15 (Q4)
unnamed: U44.5 (D3), U52.5 (D3), U64.14 (Q5)
unnamed: U44.6 (D4), U52.6 (D4), U64.13 (Q6)
unnamed: U44.7 (D5), U52.7 (D5), U64.12 (Q7)
unnamed: U44.24 (D6/S0), U52.24 (D6/S0), U64.19 (Q0), U65.15 (Q4)
unnamed: U44.1 (D7/S1), U52.1 (D7/S1), U64.18 (Q1), U65.14 (Q5)
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
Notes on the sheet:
G64
G77
G42
G86
2: Length bits 0-6 (7 bits), line flag MSB (0=point, 1=line)
G79
Gate 6
G10
G67
G29
Gate 2
G78
G74
G41
MSB Not needed
Sprite
G43
L55
G53
G20
NBL & NBM Loader Y
4: Offset Y
G38
G40
G62
Sprite frame
L28
G37
Counter 13
G33
Vector write X / Sprite write to field
G73
Decoder 59
G15
Gate 9
G52
G66
L27
G63
Clock enable latch

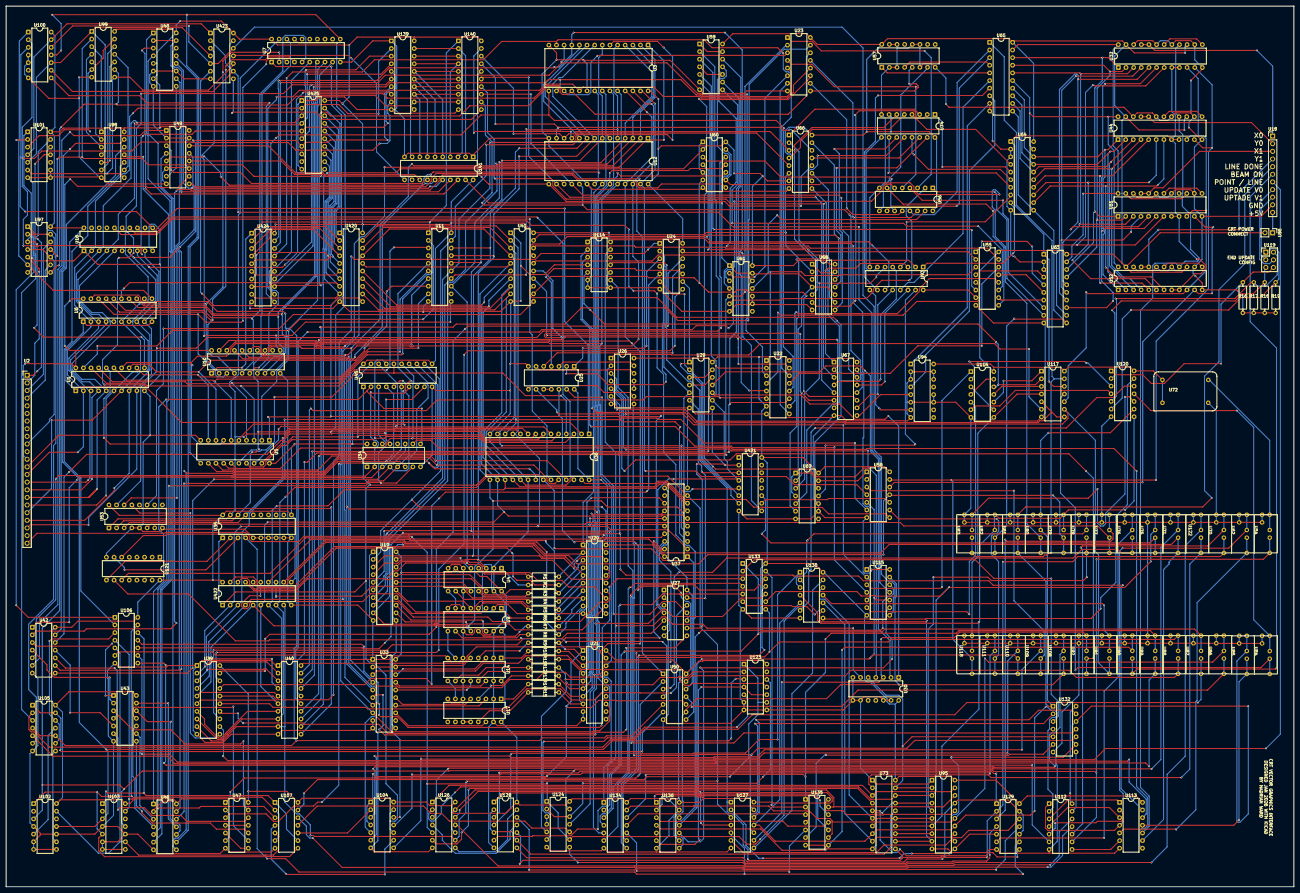
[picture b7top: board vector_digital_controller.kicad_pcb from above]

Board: 2 copper layers, 428.5 x 293.0 mm, 156 parts (0 on the bottom side), 530 nets.

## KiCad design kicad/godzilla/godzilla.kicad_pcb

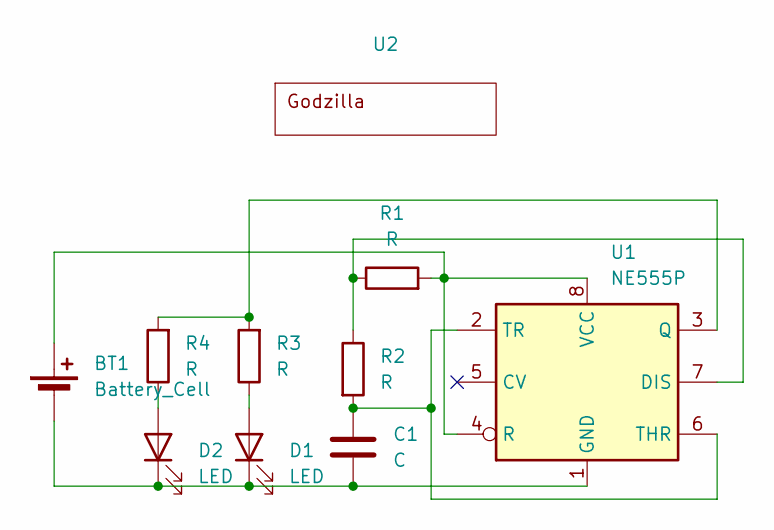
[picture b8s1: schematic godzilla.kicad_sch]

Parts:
BT1: Battery_Cell; battery_holder_coin
C1: C; CP_Radial_D4.0mm_P2.00mm
D1, D2: LED; LED_0603_1608Metric_Pad1.05x0.95mm_HandSolder
R1, R2, R3, R4: R; 0.4_pitch_resistor
U1: NE555P; DIP-8_W7.62mm
U2: godzilla_silkscreen

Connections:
unnamed: BT1.1 (+), R1.2, U1.4 (R), U1.8 (VCC)
unnamed: BT1.2 (-), C1.2, D1.1 (K), D2.1 (K), U1.1 (GND)
unnamed: D1.2 (A), R3.1
unnamed: D2.2 (A), R4.1
unnamed: R1.1, R2.1, U1.7 (DIS)
unnamed: R3.2, R4.2, U1.3 (Q)
unnamed: C1.1, R2.2, U1.2 (TR), U1.6 (THR)
